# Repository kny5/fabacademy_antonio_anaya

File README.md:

## Welcome to your new ALTERNATIVE Fab documentation site

Visit [fabacademy.org](https://fabacademy.org/) for class and other information.

I'm making this because of [this entry on the fablabs discourse forum](https://forum.fablabs.io/t/what-happened-to-gitlab-for-documentation-similar-fabacademy/49298?u=kny5)

* This website is built and published automatically using [GitHub CI](https://docs.github.com/en/actions/automating-builds-and-tests/about-continuous-integration), every time you edit the files in the docs folder
* The markdown content is generated into a site using the Mkdocs tool, a static site generator written in Python
* You can start by customizing the file `mkdocs.yml` with your information
  * To change the looks of your website, use the theme options found in the `mkdocs.yml` file or see the names of the available themes
* If you want to start a website from scratch, you can delete everything in this repository and push your own static website

## Project layout

    mkdocs.yml    # The site configuration file.
    docs/         # All site content/files should be in this folder.
        index.md  # The homepage.
        files/    # Put files you'd like available in your site here (except videos)
        images/   # You can put your images in here
        abc.md... # Other markdown pages and folders

Read more about MkDocs at [mkdocs.org](http://www.mkdocs.org).

## Building mkdocs locally

To work locally on your computer with this project, you can start with the following the steps:

> Remember to setup your SSH keys to work locally, see [GitLab Docs](https://docs.gitlab.com/ee/gitlab-basics/create-your-ssh-keys.html)

1. Clone or download this project on your computer
	* Find the clone url at the top of your projects "overview" page
	* Run `git clone git@gitlab.fabcloud.org:your/project/path.git`
1. [Install](http://www.mkdocs.org/#installation) MkDocs on your computer
1. Preview your project: `mkdocs serve`, your site can be accessed under `localhost:8000`
1. To add new pages, create the markdown file in the `docs/` folder (i.e. `touch docs/about.md`)
1. Push your changes to GitLab to automatically publish your changes
	* `git commit -m "Updated site"`
	* `git push master`

#### Git global setup

Do not forget to configure your local git environment, with same details used on Gitlab-Fabcloud.
```
git config user.name "You Name"
git config user.email "you@example.org"
```

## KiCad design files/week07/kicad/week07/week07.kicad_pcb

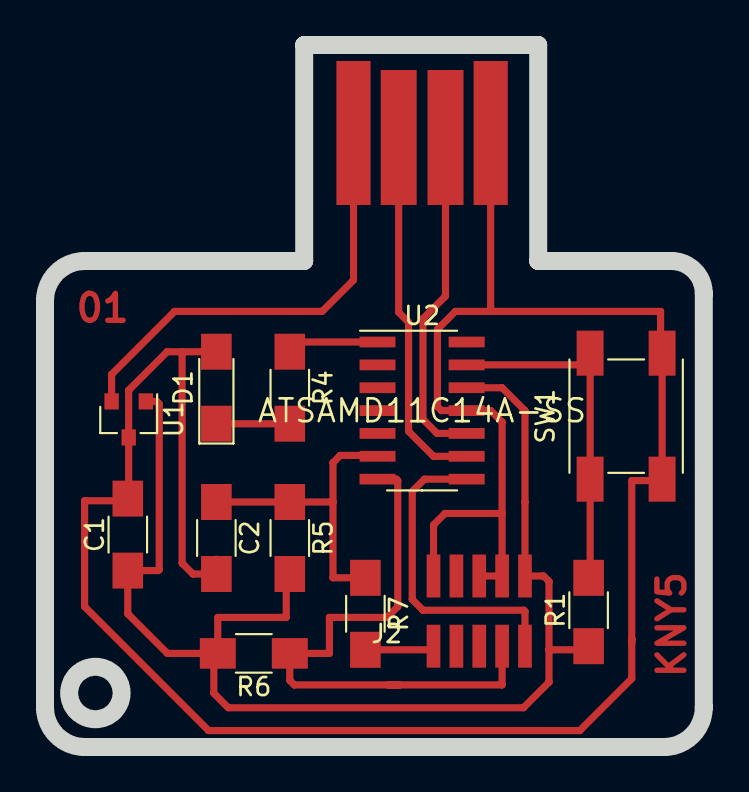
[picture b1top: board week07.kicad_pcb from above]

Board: 2 copper layers, 36.6 x 39.0 mm, 13 parts (0 on the bottom side), 12 nets.

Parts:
C1: 1uF; C_1206
C2: 1 uF; C_1206
D1: LED; LED_1206
J1: USB_A_PLUG; fab-USB_A_male_plug
J2: Conn_ARM_JTAG_SWD_10; fab-SWD10pin127pitch.lib
R1, R4: 100 Ohms; R_1206
R5, R6: 10 KOhms; R_1206
R7: 0 Ohms; R_1206
SW1: BUTTON_B3SN; Button_Omron_B3SN_6x6mm
U1: Regulator_Linear_LM3480-3.3V-100mA; SOT-23
U2: ATSAMD11C14A-SS; SOIC-14_3.9x8.7mm_P1.27mm

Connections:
CLK: J2.4, R6.1, U2.7
D+: J1.3, U2.10
D-: J1.2, U2.9
DIO: J2.2, U2.8
GND: C1.2, C2.2, D1.2, J1.4, J2.3, J2.5, J2.9, SW1.2, U1.3, U2.11
unnamed: D1.1, R4.2
unnamed: J2.10, R7.2
unnamed: R1.2, SW1.1, U2.13
unnamed: R4.1, U2.1
RESET: C2.1, R5.1, R7.1, U2.6
V3.3: C1.1, J2.1, R1.1, R5.2, R6.2, U1.1, U2.12
VCC: J1.1, U1.2

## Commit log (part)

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2018-09-19 initial import
2018-09-19 fixed stuff
2018-09-20 Upload New File
2018-09-21 added week templates
2018-09-21 Update final-project.md, added new sections
2018-09-21 Add new file
2019-01-16 updated for fabacademy 2019
2020-02-13 CI: Measure time taken for all operations
    Useful for debugging what is slow
2021-01-20 Adds website url to mkdocs config
2021-01-25 change
2021-01-25 another
2021-01-31 Adding name and social media to mkdocs yml file, 1/3 assignments, to-do:Bio, and final project
2021-02-01 Adding personal bio page, 2/3 assignments, to-do:final project
2021-02-02 3/3 final project basic description done.
2021-02-02 Adding demo asciinema, 3/3 assignments, to-do:Include images on final project
2021-02-02 Fix styling colors in theme
2021-02-02 Added mkdocs extra.css styling file and config
2021-02-02 Added mkdocs extra.css styling file and config to docs dir
2021-02-03 Added project management first timeline
2021-02-03 Added details in project management
2021-02-03 Added details in style magenta color in h3 and accent
2021-02-03 Added details in style grey backgroud
2021-02-08 week 3 2/4 CAD xdesign, inkscape, freecad
2021-02-08 week 3 2/4 directory structure changed
2021-02-08 week 3 2/4 blender files
2021-02-08 week 3 2/4 Bug: Images not loading with HTML code, testing Markdown
2021-02-09 week 3 3/4 3D files and images xdesign
2021-02-09 week 3 3/4 3D description started
2021-02-09 week 3 3/4 3D renders added description started
2021-02-09 week 3 3/4 description started _2
2021-02-09 week 3 3/4 description started _3
2021-02-09 week 3 3/4 description started _4
2021-02-09 week 3 3/4 description started _5
2021-02-10 week 3 4/4 inkscape files_2
2021-02-10 week 3 4/4 asciinema for video compression files_3
2021-02-10 week 3 4/4 asciinema for video compression files_4
2021-02-10 week 3 4/4 asciinema for video compression files_6
2021-02-10 week 3 4/4 asciinema for video compression files_7
2021-02-10 week 3 4/4 asciinema for video compression files_8
2021-02-10 week 3 4/4 files for blender render
2021-02-10 week 3 final project add postip
2021-02-10 week 3 styling padding h3
2021-02-10 week 3 structured changed on week assingment
2021-02-14 week 4, CI not updating style on extra.css
2021-02-14 week 4, CI not updating style on extra.css _fix:1
2021-02-14 week 4, CI not updating style on extra.css _fix:2
2021-02-14 week 4, CI not updating style on extra.css _fix:3
2021-02-14 week 4, CI not updating style on extra.css _fix:5
2021-02-15 week 4, style changed
2021-02-17 week 4, photos and python program
2021-02-17 week 4, photos and python program, fix .idea
2021-02-17 week 4, finished
2021-02-18 week 5, started
2021-02-23 week 5, 1/4
2021-02-24 week 5, 3/4
2021-02-24 week 5, 3.5/4
2021-02-24 week 5, 3.6/4
2021-02-24 week 5, 3.7/4
2021-03-01 week 6, started
2021-03-02 week06, 1/6
2021-03-02 week06, 2/6, missing photos.
2021-03-03 week06, missing SLA process details and images.
2021-03-03 week06, added SLA process details and missing images.
2021-03-03 week06, missing details of outcome printing
2021-03-03 week06, added some details of outcome printing
2021-03-03 week06, added files links
2021-03-06 week 7, started
2021-03-07 week 7, 1/4 missing notes and workflow
2021-03-07 week 7, 2/4, added images of usage, workflow, missing description, steps
2021-03-08 week 7, 2.1/4, added images, missing pcb design process
2021-03-08 week 7, 2.2/4, changed drop-down style
2021-03-09 week 7, 2.5/4, added phots missing description
2021-03-09 week 7, 3/4, added flashing missing pcb desc
2021-03-10 week 7, 3.5/4, added intro and descriptions, missing group assingment
2021-03-10 week 7, 3.6/4, added files link
2021-03-10 week 7, 3.7/4, fixed links and a few typos
2021-03-10 week 7, 3.9/4
2021-03-10 week 7, 3.91/4
2021-03-10 week 7, added group work
2021-03-12 week08 started
2021-03-15 week 8, started
2021-03-16 week08, files ans photos added, missing description and workflow
2021-03-16 week08, added files link from gitlab zip
2021-03-16 week08, fixed links
2021-03-16 week08, added prep description
2021-03-16 week08, commit --test
2021-03-16 week08, missing description of CAM
2021-03-16 week08, missing multiple contour operations
2021-03-17 week08, --current
2021-03-17 week08, finished
2021-03-21 week09, started
2021-03-23 week09, added scroll-program
2021-03-23 week09, added scroll code
2021-03-23 week09, fixed main video in index.md
2021-03-24 week09, missing descriptions
2021-03-24 week09, missing descriptions 2
2021-03-24 week09, missing descriptions 3
2021-03-24 week09, missing descriptions 5
2021-03-24 week09, added samd11 tables
2021-04-03 week10, started
2021-04-03 week10, missing fusion 360 workflow and images
2021-04-05 fix nueval week05 electronics production feedback
2021-04-05 fixed week07, based on nuevals feedback
2021-04-05 fixed week07 links
2021-04-06 week10, fixed video simulation link
2021-04-06 week02, fixed based on nueval feedback Moved the git tutorial from week01 to week02, Added more details about uploading content to the git repository, Added useful commands to manage video and images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
2021-04-06 week02, fixed gitlab missing keygen process
2021-04-07 week10, added ugs captures and steps
2021-04-07 week10, added group link
2021-04-13 week11, started
2021-04-13 week11, fiex images urls
2021-04-14 week11, add description missing RFID and spectrometer
2021-04-14 week11, added rfid
2021-04-14 week11, added spectral sensor current work
2021-04-14 week11, added flashing img
2021-04-17 nueval, global, week05, Screencapture for device recognition
2021-04-18 nueval, local, week01, added project sketches, description and users.
2021-04-18 nueval, local, week01, added link to fab charter
2021-04-18 nueval, local, week02, added video examples
2021-04-18 nueval, local, week02, added description to videos
2021-04-18 week12, added images and video, started
2021-04-18 week12, added script for img and video html tags for documentation process
2021-04-18 week12, fixing wrong hero img
2021-04-19 week12, added day 2 images and videos for casting
2021-04-19 week12, added day 2 images and videos for bismuth cast
2021-04-20 week12, arranged photos and videos
2021-04-20 week12, added descriptions
2021-04-20 added fusion 360
2021-04-20 added fusion images, missing description
2021-04-20 week12, added hero to homepage and img about flow sensor on week12
2021-04-26 week13, started documentation, added datasheet pdfs to repository
2021-04-27 week13, added code, circuits and demos
2021-04-27 week13, added video links
2021-04-27 week13, fixed imgs links
2021-04-27 week13, fixings in format
2021-04-28 Week13, finishing doc, added videos for lcd and hero
2021-04-28 wee13, added board11
2021-04-28 wee13, wl134
2021-04-28 wee13, fixed samd11 micro name from Quentin feedback
2021-04-28 nueval, local, week01, added context of final project
2021-04-29 week14, started with lora introduction
2021-04-29 week14, index week14 header
2021-05-04 week14, missing demo and ciurcuit schematic
2021-05-04 week14, group assingment and Theos board details
2021-05-04 week14, added filters reference
2021-05-05 week14, added LORA test images, missing description
2021-05-05 week14, added LORA test description
2021-05-05 week14, added mux table
2021-05-05 week14, added lora and images
2021-05-05 week14, added files
2021-05-10 week15, added introduction and code for micro and Python, missing links to group assingment, and refrerences.
2021-05-12 week15, recovery1
2021-05-12 week15, added files
2021-05-12 week15, fixed hero video
2021-05-12 week15, fixed files list
2021-05-12 week15, fixed mcurses
2021-05-18 nueval, local, week 03, added xdesign images, missing description, recovery1, ELF error
2021-05-18 week16, added index entry
2021-05-19 week16, added niryo 00 and 01 videos
2021-05-19 week16, added grid dims
2021-05-19 week16, added niryo link
2021-05-19 nueval, local, week 03, added more details to modeling
2021-05-19 week16, fixed clamps img
2021-05-24 nueval, local, week 10, changes based on Lucs feedback
2021-05-24 nueval, local, week 10, added design improvements
2021-05-24 nueval, local, week 09, added mouse-scroll config
2021-05-24 nueval, local, week 09, added description of mcurses
2021-05-25 nueval, local, week 14, added description of DAC, more details of usage and diagram at the end, nd files
2021-05-25 nueval, local, week 09, fixed asciinema and youtube example.
2021-05-26 week17, started.
2021-05-26 week17, added description to images
2021-05-26 week17, added dac video
2021-06-16 final, added video
2021-06-16 final, added presentation png
2021-06-16 final, added presentation mp4
2021-06-17 final, added presentation png typo fixed
2021-06-17 nueval, local, week 11, added more information about step response and fixed linked files
2021-06-17 nueval, local, week 11, added more information about hall effect
2021-06-17 nueval, local, week 13, fixed based on Lucs feedback in nueval
2021-06-17 nueval, local, week 18, added dissemination plan
2021-06-17 week19, added content
2021-06-17 week20, integrating final project page added what and who
2021-06-17 week20, final project added BOM
2021-06-18 nueval, week06 corrected images following notes from Florent
2021-06-21 nueval, week18, added business model and license
2021-06-21 nueval, week06, added corrections based on Florents nueval feedback
2021-06-22 week18, nueval, added details on seed funding and revenue streams based on Luc's feedback
2021-07-02 week19, nueval, added details on time management
2021-07-02 week19, nueval, added time management details
2021-07-02 week17, added correction on evaluation section
2021-07-03 week06, fixed typos
2021-07-05 week04, added corrections based on Luc's feedback on nueval
2021-07-05 week13, nueval, global, added fix to voltage divider circuit
2021-07-05 week07, nueval, global, added drc and captures
2021-07-06 nueval 85,70
2021-07-06 week04, added photos of iron, group and vinyls
2021-07-06 week01 fixed project management table and fab charter.
2021-07-06 final, added BOM
2021-07-06 final, added license
2021-07-06 added files for 3d print
2021-07-06 final, added files for laser
2021-07-07 final, added files milling, arduino caps, boms, 3d models
2021-07-07 final, added electronics img references
2021-07-07 final, added pcb images
2021-07-07 final, added assembly imgs and test video
2021-07-07 final, added original files
2021-07-07 added program head autor
2021-07-07 final, added tables in assembly
2021-07-07 main, added final project to index
2021-07-07 final added test video 5
2021-07-07 final added prices
2021-07-08 latest work
2021-07-08 added cost estimation for roland srm20 and fixed layour of evaluation
2021-07-08 added video evaluation 500
2021-07-08 added cost estimation
2021-07-08 added demo video
2021-07-08 added user interface
2021-07-08 corrected ui img
2021-07-08 added answers and about ph
2021-07-08 fixed thermistor img
2021-07-08 fixed code
2021-07-09 nueval, final_project, added list files at the end and missing buttons zip with kicad files
2021-07-12 nueval, final_project, updated price list
2021-07-12 nueval, final_project, updated costs
2021-07-12 nueval, final_project, updated description
2021-07-12 nueval, fixed uncompleted urls in BOMs
2021-07-12 Nueval, Global, week12, added images of roland modela 4 process and files
2021-07-12 nueval, global, week12, added files toolpath of milling
2021-07-12 nueval, global, week12, fixed imgs and stl viewer
2021-07-12 nueval, global, week12, trying to fix stl view
2021-07-12 nueval, global, week12, added soliworks img
2021-07-15 week12, note
2021-07-17 nueval, global, week12, added intro to digiscope
2021-07-18 week12, digiscope rework fixed dead links and typos
2021-07-18 Week12, digiscope added solid and rhino capture
2022-01-23 Replace presentation.png
2022-08-06 github postwork added github_ci for mkdocs
2022-08-06 github update reqs to fix dependency sec alert
2022-08-06 Deployed 5c84a65 with MkDocs version: 1.3.1
2022-08-06 github added MIT license
2023-02-07 2023, added github ci file
